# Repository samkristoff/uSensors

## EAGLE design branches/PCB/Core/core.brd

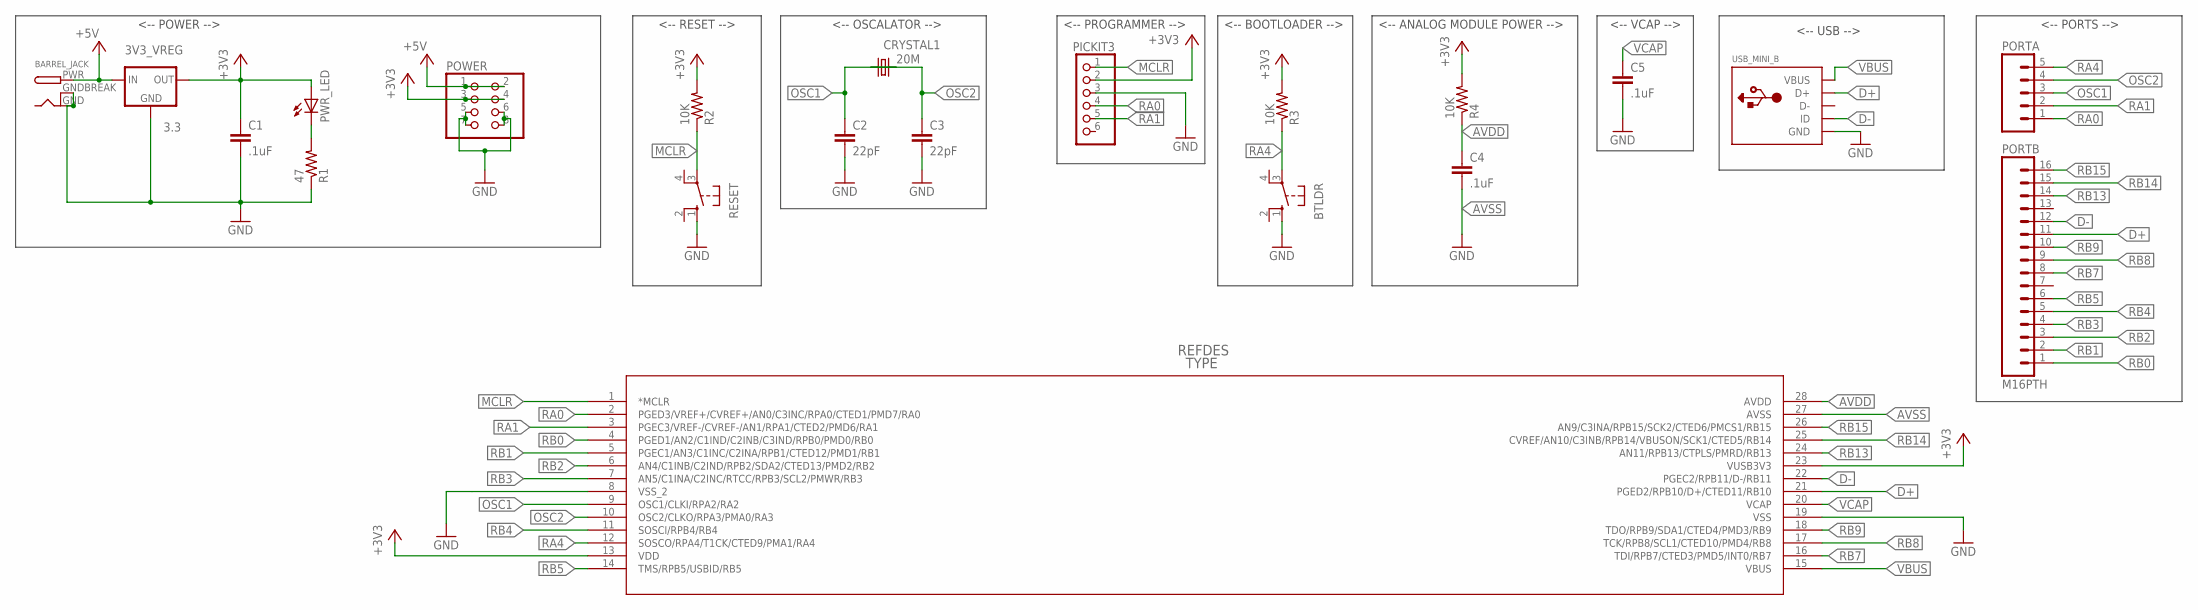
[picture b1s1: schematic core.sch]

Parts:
3V3_VREG: 3.3; TO-220-ALT
BARREL_JACK: DCBARRELPTH; DCJACK_2MM_PTH
BTLDR: 10-XX; B3F-10XX
C1, C4, C5: .1uF; C2.5-2
C2, C3: 22pF; C2.5-2
CRYSTAL1: 20M; HC49U-V
PICKIT3: PINHD-1X6; 1X06
PORTA: M05PTH; 1X05
PORTB: M16PTH; 1X16
POWER: PINHD-2X4; 2X04
PWR_LED: LED5MM
R1: 47; 0207/10
R2, R3, R4: 10K; 0207/10
RESET: 10-XX; B3F-10XX
U1: PIC32MX230F064B-; SPDIP28_300MC
USB_MINI_B: USBMOLEX; USB-MINIB-THM-MOLEX

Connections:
+3V3: 3V3_VREG.OUT, C1.1, PICKIT3.2, POWER.3, POWER.4, PWR_LED.A, R2.2, R3.2, R4.2, U1.13 (VDD), U1.23 (VUSB3V3)
+5V: 3V3_VREG.IN, BARREL_JACK.PWR, POWER.1, POWER.2
AVDD: C4.1, R4.1, U1.28 (AVDD)
AVSS: C4.2, U1.27 (AVSS)
D+: PORTB.11, U1.21 (PGED2/RPB10/D+/CTED11/RB10), USB_MINI_B.D+
D-: PORTB.12, U1.22 (PGEC2/RPB11/D-/RB11), USB_MINI_B.ID
GND: 3V3_VREG.GND, BARREL_JACK.GND, BARREL_JACK.GNDBREAK, BTLDR.1 (S), C1.2, C2.2, C3.2, C5.2, PICKIT3.3, POWER.5, POWER.6, POWER.7, POWER.8, R1.1, RESET.1 (S), U1.8 (VSS_2), U1.19 (VSS), USB_MINI_B.GND
MCLR: PICKIT3.1, R2.1, RESET.3, U1.1 (*MCLR)
unnamed: PWR_LED.K (C), R1.2
OSC1: C2.1, CRYSTAL1.2, PORTA.3, U1.9 (OSC1/CLKI/RPA2/RA2)
OSC2: C3.1, CRYSTAL1.1, PORTA.4, U1.10 (OSC2/CLKO/RPA3/PMA0/RA3)
RA0: PICKIT3.4, PORTA.1, U1.2 (PGED3/VREF+/CVREF+/AN0/C3INC/RPA0/CTED1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)
RA1: PICKIT3.5, PORTA.2, U1.3 (PGEC3/VREF-/CVREF-/AN1/RPA1/CTED2/PMD6/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)
RA4: BTLDR.3, PORTA.5, R3.1, U1.12 (SOSCO/RPA4/T1CK/CTED9/PMA1/RA4)
RB0: PORTB.1, U1.4 (PGED1/AN2/C1IND/C2INB/C3IND/RPB0/PMD0/R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)
RB1: PORTB.2, U1.5 (PGEC1/AN3/C1INC/C2INA/RPB1/CTED12/PMD1/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)
RB2: PORTB.3, U1.6 (AN4/C1INB/C2IND/RPB2/SDA2/CTED13/PMD2/R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)
RB3: PORTB.4, U1.7 (AN5/C1INA/C2INC/RTCC/RPB3/SCL2/PMWR/RB3)
RB4: PORTB.5, U1.11 (SOSCI/RPB4/RB4)
RB5: PORTB.6, U1.14 (TMS/RPB5/USBID/RB5)
RB7: PORTB.8, U1.16 (TDI/RPB7/CTED3/PMD5/INT0/RB7)
RB8: PORTB.9, U1.17 (TCK/RPB8/SCL1/CTED10/PMD4/RB8)
RB9: PORTB.10, U1.18 (TDO/RPB9/SDA1/CTED4/PMD3/RB9)
RB13: PORTB.14, U1.24 (AN11/RPB13/CTPLS/PMRD/RB13)
RB14: PORTB.15, U1.25 (CVREF/AN10/C3INB/RPB14/VBUSON/SCK1/CTED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)
RB15: PORTB.16, U1.26 (AN9/C3INA/RPB15/SCK2/CTED6/PMCS1/RB15)
VBUS: U1.15 (VBUS), USB_MINI_B.VBUS
VCAP: C5.1, U1.20 (VCAP)

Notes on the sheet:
<-- OSCALATOR -->
<-- POWER -->
<-- BOOTLOADER -->
<-- RESET -->
<-- PROGRAMMER -->
<-- ANALOG MODULE POWER -->
<-- VCAP -->
<-- USB -->
<-- PORTS -->

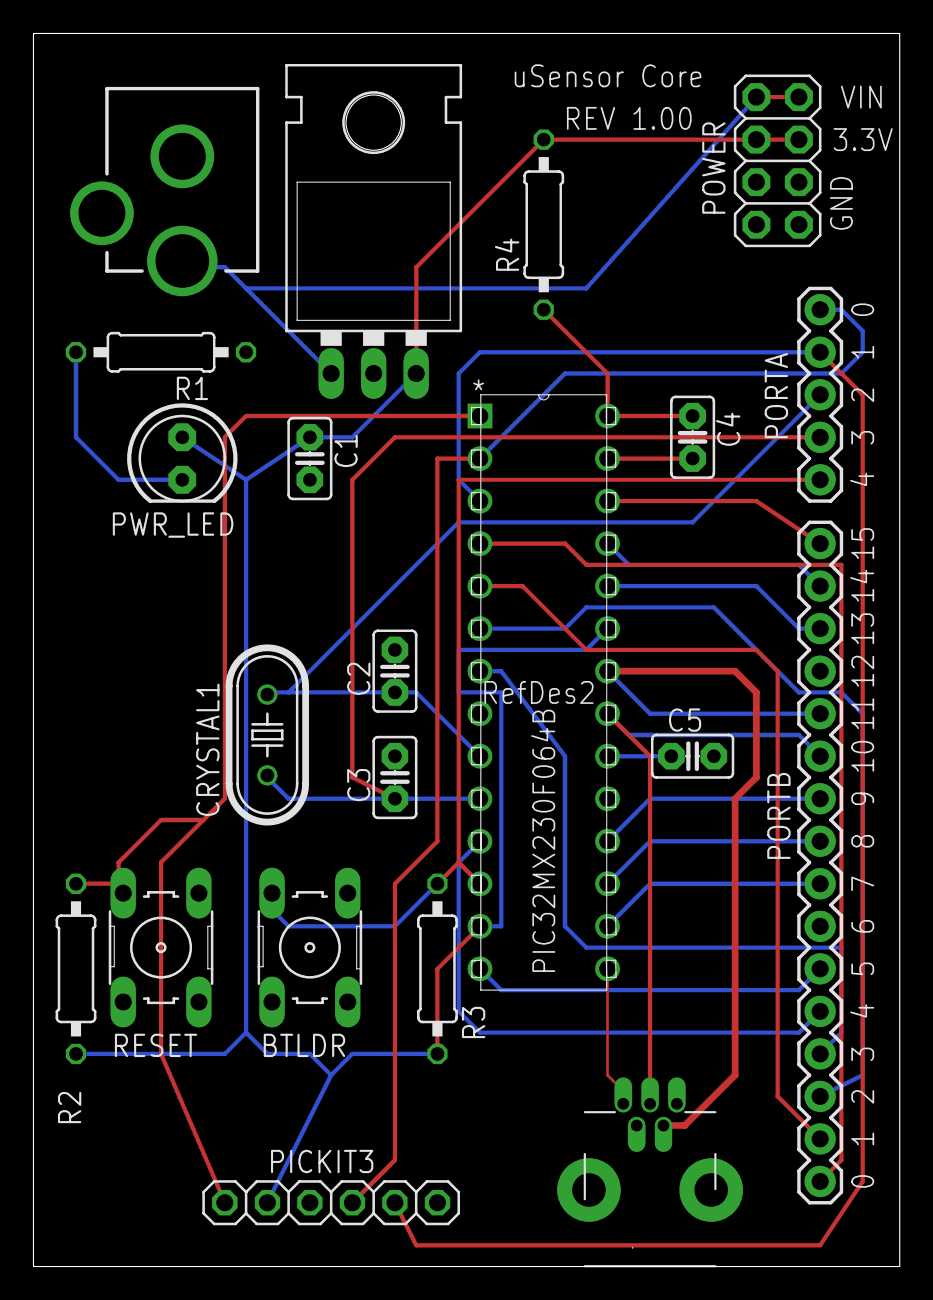
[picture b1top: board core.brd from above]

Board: 2 copper layers, 51.7 x 73.7 mm, 21 parts (0 on the bottom side), 28 nets.

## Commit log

2013-02-16 Added uSensor Bootloader
    Added fully working USB bootloader code for PIC32MX230F064B
2013-02-16 Update bootloader readme
    Added info about how to break into the bootloader.
2013-02-17 Added Simple CDC Project
    Working CDC firmware that works with USB bootloader.
2013-02-23 Adding Core PCB
    Core PCB In Work
2013-02-23 Completed Core Schematic
    Needs to check schematic and create layout
2013-02-24 Working on Routing
    Going to try simplifying VSS / GND
2013-02-24 Pre Gerber for Rev 1.00
2013-04-06 Minor Updates
2013-04-06 Minor Update

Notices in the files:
parts and their libraries:
SparkFun-PowerIC: Licensing: CC v3.0 Share-Alike You are welcome to use this library for commercial purposes.
